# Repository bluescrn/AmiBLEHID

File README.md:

# AmiBLEHID

Work in progress, but now fairly functional. Needs a better name.

*Another new iteration, v0.5 PCB shrunk down to fit A600. No 3D printable case for this one yet. Nobody seems to make a DE-9 connector without the 'ears', but if you try to snip them off a regular one, the metal parts fall apart, leaving the central plastic part which can be used as-is*

## What is it?

With minimal other components (essentially just a [74HC05](https://www.build-electronic-circuits.com/7400-series-integrated-circuits/74hc05-74ls05/) and the joystick port connector), an ESP32-H2 module can be connected to an Amiga joystick/mouse port, and allow a Bluetooth LE mouse or controller to be used with the Amiga.

There is an existing project, [Unijoysticle](https://github.com/ricardoquesada/unijoysticle2), that uses an ESP32-WROOM32 and provides compatibility with far more devices by supporting Bluetooth Classic, but it's a relatively bulky board and I believe it requires external power. This is an attempt to build a smaller neater single-port 'dongle' using the same approach, albeit with more limited functionality.

The H2 has no wifi, and only supports BLE (no Bluetooth Classic). Other ESP32 modules likely draw too much current. With the latest revision, I measured power consumption as between 22mA and 34mA, depending on the amount of BLE activity.

## Features

- Mouse speed control (cycle 5 levels via button on board, or press mouse button 4 if the mouse has one)
- Mouse emulation using right analog stick when using a controller and Amiga joystick port 1
- 'Up-to-jump' mode - Maps the 2nd button to joystick up
- Experimental CD32 protocol support (7 buttons)
 
## Code

The code side of things is based around [NimBLE Arduino](https://docs.arduino.cc/libraries/nimble-arduino/) and [this HID report parsing code](https://github.com/pasztorpisti/hid-report-parser), and can be built in the Arduino IDE

Had to add a little bodge to the HID parser to read the hat switch (d-pad) properly, as the neutral position of a hat switch (usually 0 or -1 depending on device) is outside the logical_min/max range of the axis, and the parser was ignoring out-of-range values.

## Limitations

BLE game controllers are very uncommon, the only common+good ones that I'm aware of are the latest model of Xbox controller and the 8BitDo Ultimate Wireless 2.
  
~~Only supports two joystick/mouse buttons~~. Now has mostly-functional CD32 protocol support. Good enough for casual gaming, but a little bit glitchy (dropped/spurious button presses) due to issues with ESP32 interrupt timing stability.

The USB-C port on the ESP32 module isn't currently supported for wired mice/controllers. Would be nice to support wired controllers, but the additional current draw is likely to be too much for the Amiga joystick port

## Tested+Compatible devices

Amigas
- Only tested on an A1200. Have tested with two of them and so far it seems OK (see [this thread](https://eab.abime.net/showthread.php?t=98463) for some discussion of joystick port current limits)
- Probably won't fit an A600. Space around the joystick ports looks very tight? (could use a joystick extension cable maybe, but that defeats the goal of a small+neat dongle)

Controllers:
- Xbox Series S/X controller (this is the version with USB-C and the extra 'share' button in the centre. Previous versions aren't BLE)
- 8BitDo Ultimate 2 Wireless

Mice:
- KeyChron M3 Wireless Mouse
- Logitech MX Anywhere 3
- Razer Atheris

## Status LED
Fast blue blinking - BLE pairing (Hold reset button for ~3 secs until both LEDs flash orange to enter pairing mode)
Slow blue blinking - BLE scanning/connecting (to paired device)
Red - BLE scanning timed out, not connected
Cyan   - Mouse connected
Green  - Controller connected, Regular 2-button mode
Purple - Controller connected, CD32 mode (when the Amiga software is treating it as a CD32 controller)

Status LED brightness will increase slightly when a mouse button or controller button A/B is held. Mostly to show it's connected. (Might be able to use it to approximately measure latency by pointing a camera at it and recording the LED and button being pressed?)

## Mode LED
With a mouse connected, the mode LED will cycle between green (slowest) and red (fastest) as you cycle through mouse speed (middle mouse button, or Mode button on the board)

With a controller connected, the mode LED will switch between green (normal) and yellow (up-to-jump mode) when the mode is switched (start button or Mode button). Up-to-jump mode won't work if the controller is being read as a CD32 pad.

## CD32 Protocol

A real CD32 controller contains a shift register chip, used to output the state of 7 buttons serially, when pin 9 is pulled low and pin 6 (Fire 1) is pulsed as a clock. During this process the button state is output to pin 9 (Fire 2)

There is an initial attempt to support this. The status LED will switch from green to purple when CD32 button reading is detected (pin 9 changing level).

But emulating the shift register behaviour in code requires quite responsive interrupts, and regular ESP32 interrupts on the H2 (single-core 96MHz RISC-V) aren't quite fast/stable enough for this. While it's mostly functional, there are currently some dropped and spurious button inputs picked up due to the interrupts being delayed. I've tried to optimize the C code a bit by using ESP-IDF functions for the interrupt handling rather than the Arduino wrapper, which may have helped a bit, but it's not 100%.

It looked like this should be resolvable in software by moving everything to ESP-IDF and using a high-priority interrupt (written in assembly language), but that solution only applies to Xtensa-based ESP32s, no the RISC-V-based ESP32-H2.

I've been testing CD32 support with [Joytest_CP](https://aminet.net/package/driver/input/joytest_CP) and also with [Cecconoid](https://thalamusdigital.itch.io/cecconoid-amiga).

([JoyPortTest](https://aminet.net/package/driver/input/JoyPortTest.lha) didn't work initially, but it turns out that a real CD32 pad will output a zero then a one after the 7 button bits, so 9 bits shifted out in total. After tweaking the ESP32 code to add the extra two bits, JoyPortTest can detect+read it as a CD32 pad.

After investigating further with an oscilloscope, I could see that Joytest CP actually samples the CD32 buttons 7 times in rapid succession, once per call to the Blitz Basic 'JoyB()' function. It's a bit more stable if only sampling it once per frame, triggering a lot fewer interrupts. Could also see that responding to the rising edge of the clock signal was better than the falling edge, giving the interrupt slightly more time to respond. But I could also see that every now and again, pulses would shift by the duration of a whole pulse or more - there's definitely something delaying the response to the GPIO interrupts - I'm guessing at critical sections or higher-priority interrupts relating to Bluetooth, but don't know for sure and don't have any solid ideas to improve it further on the software side yet.

Image shows the normal case when it's working well - The ISR seems to be responding within a few microseconds most of the time, but sometimes the output pulses are delayed quite significantly, causing spurious or dropped button presses.

There are only 7 clock pulses when testing with JoyTestCP (which uses the Blitz Basic 2 function to read the buttons), but with JoyPortTest there are 2 additional pulses, which it expects to return 0 then 1 and uses this to detect the presence of a CD32 controller.

## USB controllers?

The ESP32-H2 board has a USB-C connector. It would be nice if it could also support wired USB controller, but I don't think the ESP32-H2 can function as a USB host, and if it could, power draw would likely be too much (especially controllers with rumble motors and RGB lighting). So don't try plugging anything in when it's connected to the Amiga unless you're connecting it to a PC for programming/debug output.

## Mouse Wheel Support

There is now an experimental implementation of mouse wheel and middle button support. Instead of attempting to implement the Cocolino protocol, the CD32 controller protocol is used to pass additional button states to the Amiga. This avoids any messing with the quadrature outputs and was simple to implement on the ESP32 using the existing CD32 controller logic. But it has the same issue with ESP32 interrupt timing and may suffer from occasional dropped/spurious inputs. In practice, it seems fairly reliable though

This requires a driver on the Amiga to read the additional buttons from a vblank interrupt handler and create the mouse wheel events. The driver is a modified version of the [TankMouse]( https://aminet.net/package/driver/input/TankMouse) driver.

## BOM

|Qty|Component|
|--|----|
|1x|[Waveshare ESP32-H2 Zero](https://www.waveshare.com/esp32-h2-zero.htm)|
|1x|74HC05 open-collector hex inverter (SOIC)|
|2x|Micro tactile pushbutton switch (4.5x4.5x4.5mm)|
|2x|WS2812B RGB LEDs (3535 size)|
|1x|9-pin female D-Sub connector (solder bucket connections)|
|2x|1N4148 diodes (SOD-123)|
|1x|470 ohm resistor (3216 Metric)|

The LEDs are likely the trickiest part to source as the larger 5050 size are more common. I'd bought a load from AliExpress for another project so already had some.

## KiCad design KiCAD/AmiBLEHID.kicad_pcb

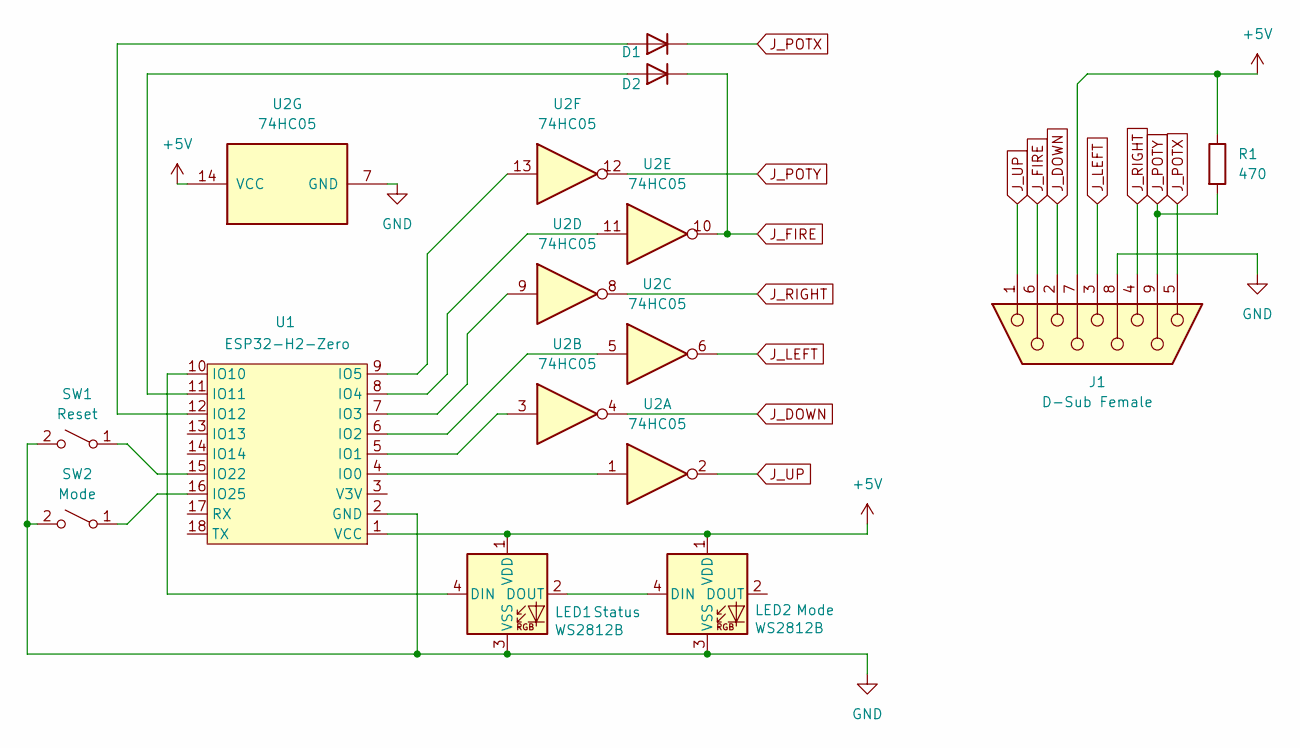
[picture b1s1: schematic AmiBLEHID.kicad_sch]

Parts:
D1, D2: 1N4148; D_1206_3216Metric
J1: D-Sub Female; DSUB-9_Socket_EdgeMount_P2.77mm
LED1, LED2: WS2812B; LED_WS2812B-Mini_PLCC4_3.5x3.5mm
R1: 470; R_1206_3216Metric
SW1: Reset; SW_SPST_PTS647_Sx50
SW2: Mode; SW_SPST_PTS647_Sx50
U1: ESP32-H2-Zero; Waveshare-ESP32-H2-Zero
U2: 74HC05; SO-14_5.3x10.2mm_P1.27mm

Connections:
+5V: J1.7, LED1.1 (VDD), LED2.1 (VDD), R1.1, U1.1 (VCC), U2.14 (VCC)
GND: J1.8, LED1.3 (VSS), LED2.3 (VSS), SW1.2 (B), SW2.2 (B), U1.2 (GND), U2.7 (GND)
J_DOWN: J1.2, U2.4
J_FIRE: D2.1 (K), J1.6, U2.10
J_LEFT: J1.3, U2.6
J_POTX: D1.1 (K), J1.5
J_POTY: J1.9, R1.2, U2.12
J_RIGHT: J1.4, U2.8
J_UP: J1.1, U2.2
unnamed: D1.2 (A), U1.12 (IO12)
unnamed: D2.2 (A), U1.11 (IO11)
unnamed: LED1.4 (DIN), U1.10 (IO10)
unnamed: LED1.2 (DOUT), LED2.4 (DIN)
unnamed: SW1.1 (A), U1.15 (IO22)
unnamed: SW2.1 (A), U1.16 (IO25)
unnamed: U1.4 (IO0), U2.1
unnamed: U1.5 (IO1), U2.3
unnamed: U1.6 (IO2), U2.5
unnamed: U1.7 (IO3), U2.9
unnamed: U1.8 (IO4), U2.11
unnamed: U1.9 (IO5), U2.13

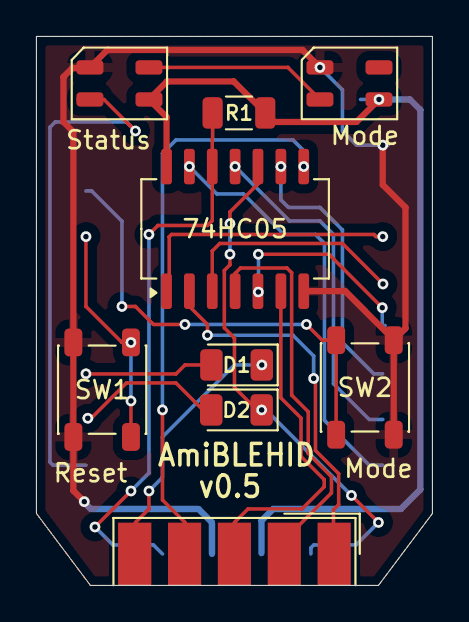
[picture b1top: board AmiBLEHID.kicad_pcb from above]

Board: 2 copper layers, 22.0 x 30.5 mm, 10 parts (1 on the bottom side), 21 nets.

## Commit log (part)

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2026-02-15 Pic of prototype
2026-04-26 WIP - Updates for new iteration with WS2812 LEDs
2026-06-22 Code updates. Better binding/reset logic, and scaling of analog/hat axis ranges so it works with 8BitDo Ultimate 2 as well as Xbox controller
2026-06-22 KiCAD project updates - *untested* 0.4 revision aimed at enabling CD32 protocol support
2026-06-23 Mouse emulation via right analog stick on controller. Also map left/right bumpers to Amiga buttons 1+2 (for use along with right stick as mouse buttons)
2026-06-23 Printable case STLs
2026-06-27 Initial attempt at CD32 controller support
